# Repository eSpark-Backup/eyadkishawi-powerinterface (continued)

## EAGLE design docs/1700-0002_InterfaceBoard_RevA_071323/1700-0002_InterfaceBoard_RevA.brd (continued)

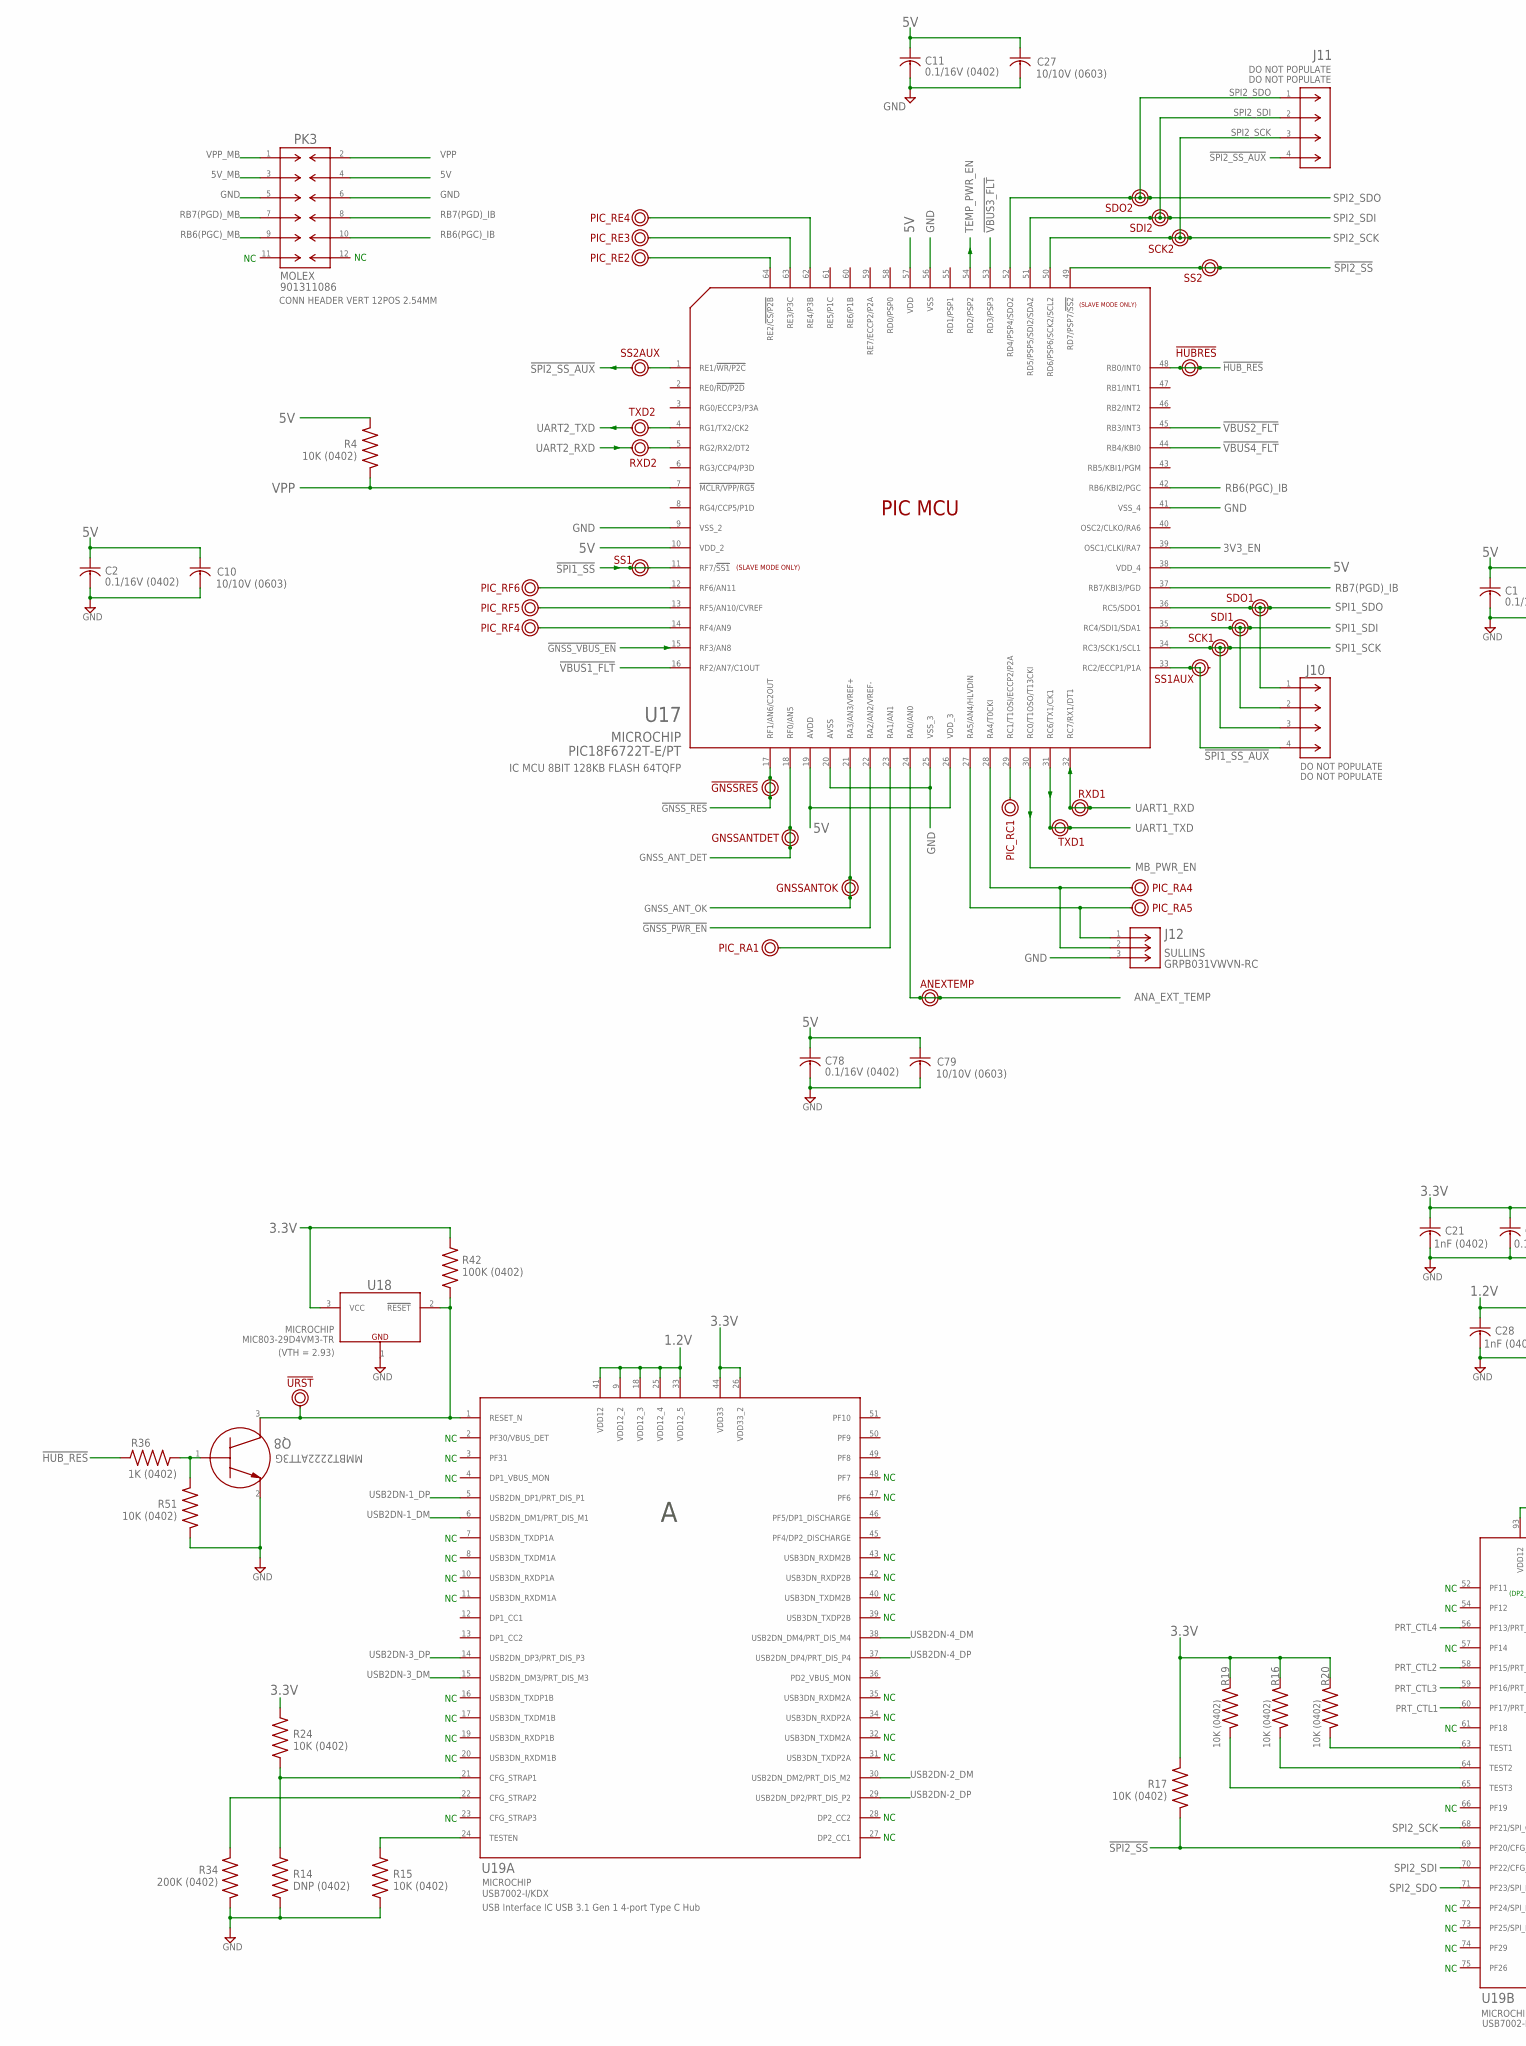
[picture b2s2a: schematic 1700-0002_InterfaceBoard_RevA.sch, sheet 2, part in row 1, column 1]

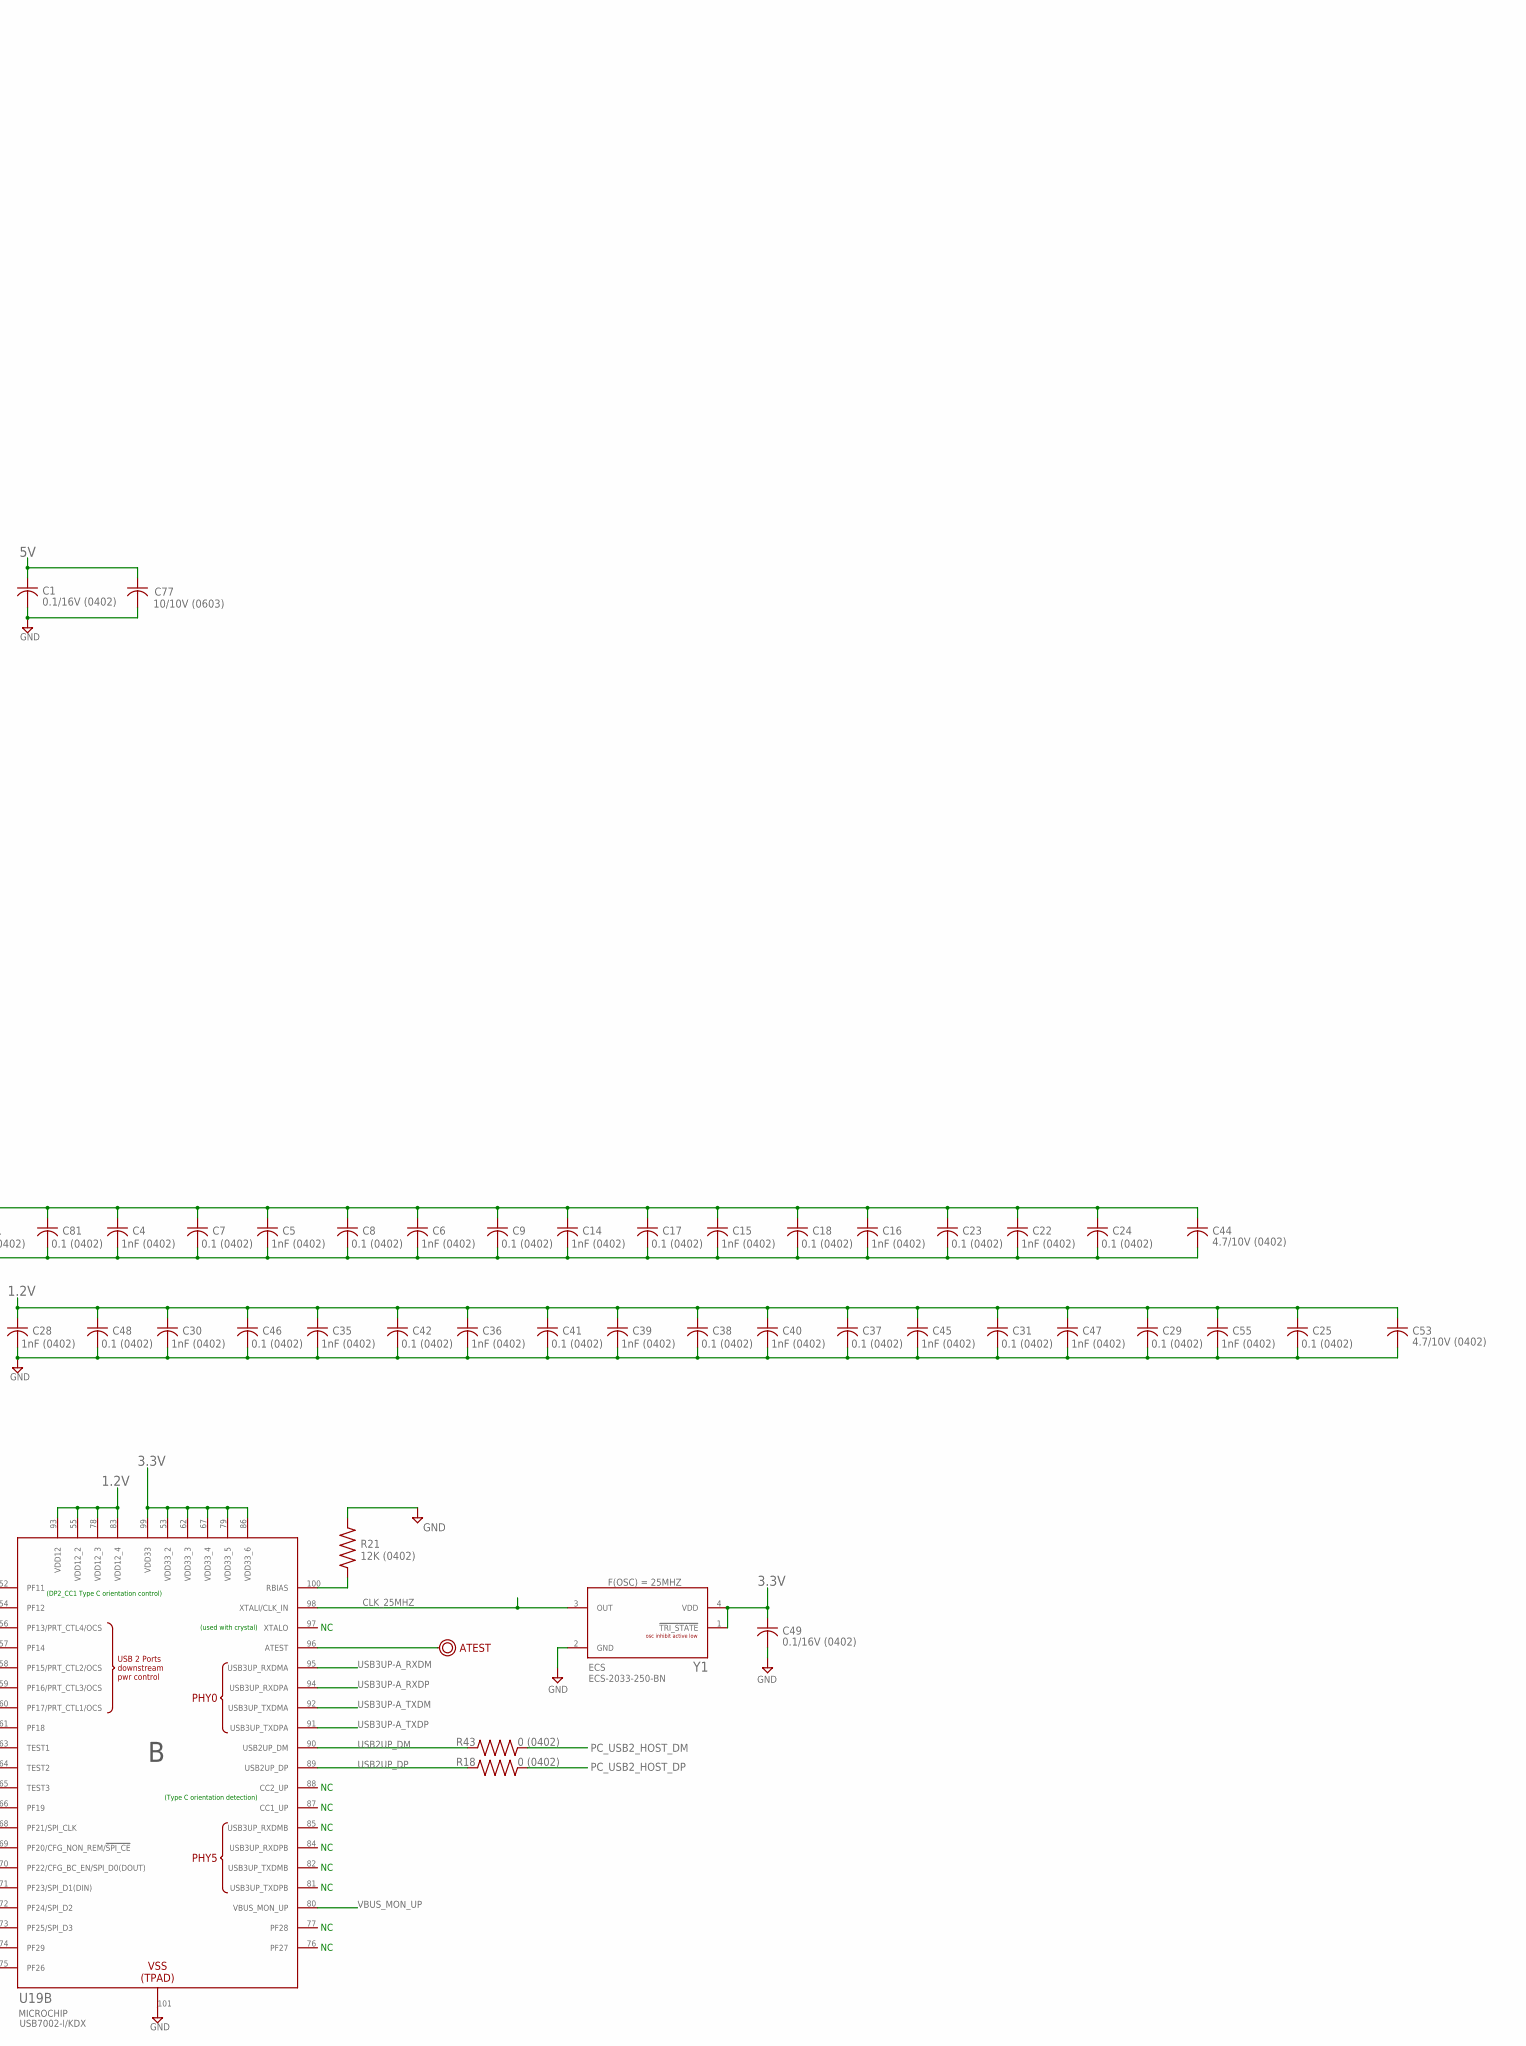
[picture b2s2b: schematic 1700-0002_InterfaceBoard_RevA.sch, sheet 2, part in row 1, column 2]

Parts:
!GNSSRES: TST_POINT_PTH_20X40MIL_2PIN
!HUBRES: TST_POINT_PTH_20X40MIL_2PIN
!URST: TST_POINT_PTH_042-OCT
ANEXTEMP: TST_POINT_PTH_20X40MIL_2PIN
ATEST: TST_POINT_PTH_042-OCT
C1, C2, C11, C49, C78: 0.1/16V (0402); G-155_MUR
C4, C5, C6, C14, C15, C16, C21, C22, C28, C30, C35, C36, C39, C40, C45, C47, C55: 1nF (0402); G-155_MUR; MANUFACTURER_PART_NUMBER C0402C102K4RAC7867
C7, C8, C9, C17, C18, C23, C24, C25, C29, C31, C37, C38, C41, C42, C46, C48, C81: 0.1 (0402); G-155_MUR
C10, C27, C77, C79: 10/10V (0603); CAP_C1608_TDK; MANUFACTURER_PART_NUMBER GRM188D71A106KA73D
C44, C53: 4.7/10V (0402); G-155_MUR; MANUFACTURER_PART_NUMBER C1005X5R1A475K050BE
GNSSANTDET: TST_POINT_PTH_20X40MIL_2PIN
GNSSANTOK: TST_POINT_PTH_20X40MIL_2PIN
J10, J11: MOLEX_VERT-HDR_1718561004; MOLEX_VERT-HDR_171861004; MANUFACTURER_PART_NUMBER DO NOT POPULATE
J12: SULLINS_MALE-HDR_050_GRPB031VWVN-RC; CONN_GRPB031VWVN-RC_SUL
PIC_RA1, PIC_RA4, PIC_RA5: TST_POINT_PTH_042-OCT
PIC_RC1: TST_POINT_PTH_042-OCT
PIC_RE2, PIC_RE3, PIC_RE4: TST_POINT_PTH_042-OCT
PIC_RF4, PIC_RF5, PIC_RF6: TST_POINT_PTH_042-OCT
PK3: CON_MOLEX_901311086; CON_901311086_MOL
Q8: MMBT2222ATT3G; SC-75(SOT-416)_ONSEMI
R4, R15, R16, R17, R19, R20, R24, R51: 10K (0402); RESC1005X35N
R14: DNP (0402); RESC1005X35N; MANUFACTURER_PART_NUMBER DO NOT POPULATE
R18, R43: 0 (0402); RESC1005X35N; MANUFACTURER_PART_NUMBER CRCW04020000Z0EDC
R21: 12K (0402); RESC1005X35N; MANUFACTURER_PART_NUMBER CRCW040212K0FKEDC
R34: 200K (0402); RESC1005X35N; MANUFACTURER_PART_NUMBER CRCW0402200KFKED
R36: 1K (0402); RESC1005X35N; MANUFACTURER_PART_NUMBER CRCW04021K00FKEDC
R42: 100K (0402); RESC1005X35N; MANUFACTURER_PART_NUMBER CRCW0402100KFKEDC
RXD1, RXD2: TST_POINT_PTH_20X40MIL_2PIN
SCK1, SCK2: TST_POINT_PTH_20X40MIL_2PIN
SDI1, SDI2: TST_POINT_PTH_20X40MIL_2PIN
SDO1, SDO2: TST_POINT_PTH_20X40MIL_2PIN
SS1, SS1AUX, SS2, SS2AUX: TST_POINT_PTH_20X40MIL_2PIN
TXD1, TXD2: TST_POINT_PTH_20X40MIL_2PIN
U17: PIC18F6627T-E/PT; TQFP64_10X10MC_MCH; MANUFACTURER_PART_NUMBER PIC18F6722T-E/PT
U18: (VTH = 2.93); SOT-23_M3_MCH
U19: MICROCHIP_USB7002-I/KDX; VQFN100_KDX_MCH; PART_DESC USB Interface IC USB 3.1 Gen 1 4-port T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
Y1: F(OSC) = 25MHZ; OSC_ECS-2033-250-BN

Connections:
1.2V: C25.1, C28.1, C29.1, C30.1, C31.1, C35.1, C36.1, C37.1, C38.1, C39.1, C40.1, C41.1, C42.1, C45.1, C46.1, C47.1, C48.1, C53.1, C55.1, U19.9 (VDD12_2), U19.18 (VDD12_3), U19.25 (VDD12_4), U19.33 (VDD12_5), U19.41 (VDD12), U19.55 (VDD12_2), U19.78 (VDD12_3), U19.83 (VDD12_4), U19.93 (VDD12); also elsewhere on the board
3.3V: C4.1, C5.1, C6.1, C7.1, C8.1, C9.1, C14.1, C15.1, C16.1, C17.1, C18.1, C21.1, C22.1, C23.1, C24.1, C44.1, C49.1, C81.1, R16.1, R17.1, R19.1, R20.1, R24.1, R42.1, U18.3 (VCC), U19.26 (VDD33_2), U19.44 (VDD33), U19.53 (VDD33_2), U19.62 (VDD33_3), U19.67 (VDD33_4), U19.79 (VDD33_5), U19.86 (VDD33_6), U19.99 (VDD33), Y1.1 (!TRI_STATE), Y1.4 (VDD); also elsewhere on the board
3V3_EN: U17.39 (OSC1/CLKI/RA7); also elsewhere on the board
5V: C1.1, C2.1, C10.1, C11.1, C27.1, C77.1, C78.1, C79.1, PK3.4, R4.1, U17.10 (VDD_2), U17.19 (AVDD), U17.26 (VDD_3), U17.38 (VDD_4), U17.57 (VDD); also elsewhere on the board
5V_MB: PK3.3; also elsewhere on the board
!GNSS_PWR_EN: U17.22 (RA2/AN2/VREF-); also elsewhere on the board
!GNSS_RES: !GNSSRES.P$1, !GNSSRES.P$2, U17.17 (RF1/AN6/C2OUT); also elsewhere on the board
!GNSS_VBUS_EN: U17.15 (RF3/AN8); also elsewhere on the board
!HUB_RES: !HUBRES.P$1, !HUBRES.P$2, R36.1, U17.48 (RB0/INT0)
!SPI1_SS: SS1.P$2, U17.11 (RF7/!SS1); also elsewhere on the board
!SPI1_SS_AUX: J10.4, SS1AUX.P$2, U17.33 (RC2/ECCP1/P1A)
!SPI2_SS: R17.2, SS2.P$1, SS2.P$2, U17.49 (RD7/PSP7/!SS2), U19.69 (PF20/CFG_NON_REM/!SPI_CE)
!SPI2_SS_AUX: J11.4, SS2AUX.P$2
!URST: !URST.P$1, Q8.3 (C), R42.2, U18.2 (!RESET), U19.1 (RESET_N)
!VBUS1_FLT: U17.16 (RF2/AN7/C1OUT); also elsewhere on the board
!VBUS2_FLT: U17.45 (RB3/INT3); also elsewhere on the board
!VBUS3_FLT: U17.53 (RD3/PSP3); also elsewhere on the board
!VBUS4_FLT: U17.44 (RB4/KBI0); also elsewhere on the board
ANA_EXT_TEMP: ANEXTEMP.P$1, ANEXTEMP.P$2, U17.24 (RA0/AN0); also elsewhere on the board
CLK_25MHZ: U19.98 (XTALI/CLK_IN), Y1.3 (OUT)
GND: C1.2, C2.2, C4.2, C5.2, C6.2, C7.2, C8.2, C9.2, C10.2, C11.2, C14.2, C15.2, C16.2, C17.2, C18.2, C21.2, C22.2, C23.2, C24.2, C25.2, C27.2, C28.2, C29.2, C30.2, C31.2, C35.2, C36.2, C37.2, C38.2, C39.2, C40.2, C41.2, C42.2, C44.2, C45.2, C46.2, C47.2, C48.2, C49.2, C53.2, C55.2, C77.2, C78.2, C79.2, C81.2, J12.3, PK3.5, PK3.6, Q8.2 (E), R14.2, R15.2, R21.1, R34.2, R51.2, U17.9 (VSS_2), U17.20 (AVSS), U17.25 (VSS_3), U17.41 (VSS_4), U17.56 (VSS), U18.1 (GND), U19.101 (VSS), Y1.2 (GND); also elsewhere on the board
GNSS_ANT_DET: GNSSANTDET.P$1, GNSSANTDET.P$2, U17.18 (RF0/AN5); also elsewhere on the board
GNSS_ANT_OK: GNSSANTOK.P$1, GNSSANTOK.P$2, U17.21 (RA3/AN3/VREF+); also elsewhere on the board
MB_PWR_EN: U17.30 (RC0/T1OSO/T13CKI); also elsewhere on the board
unnamed: PIC_RF6.P$1, U17.12 (RF6/AN11)
unnamed: TXD2.P$1, U17.4 (RG1/TX2/CK2)
unnamed: R14.1, R24.2, U19.21 (CFG_STRAP1)
unnamed: R34.1, U19.22 (CFG_STRAP2)
unnamed: R15.1, U19.24 (TESTEN)
unnamed: R20.2, U19.63 (TEST1)
unnamed: R19.2, U19.65 (TEST3)
unnamed: R21.2, U19.100 (RBIAS)
unnamed: R16.2, U19.64 (TEST2)
unnamed: ATEST.P$1, U19.96 (ATEST)
unnamed: PIC_RF5.P$1, U17.13 (RF5/AN10/CVREF)
unnamed: PIC_RF4.P$1, U17.14 (RF4/AN9)
unnamed: PIC_RA1.P$1, U17.23 (RA1/AN1)
unnamed: RXD2.P$1, U17.5 (RG2/RX2/DT2)
unnamed: SS2AUX.P$1, U17.1 (RE1/!WR/P2C)
unnamed: J12.1, PIC_RA5.P$1, U17.27 (RA5/AN4/HLVDIN)
unnamed: J12.2, PIC_RA4.P$1, U17.28 (RA4/T0CKI)
unnamed: PIC_RC1.P$1, U17.29 (RC1/T1OSI/ECCP2/P2A)
unnamed: PIC_RE2.P$1, U17.64 (RE2/!CS/P2B)
unnamed: PIC_RE3.P$1, U17.63 (RE3/P3C)
unnamed: PIC_RE4.P$1, U17.62 (RE4/P3B)
PC_USB2_HOST_DM: R43.2; also elsewhere on the board
PC_USB2_HOST_DP: R18.2; also elsewhere on the board
PRT_CTL1: U19.60 (PF17/PRT_CTL1/OCS); also elsewhere on the board
PRT_CTL2: U19.58 (PF15/PRT_CTL2/OCS); also elsewhere on the board
PRT_CTL3: U19.59 (PF16/PRT_CTL3/OCS); also elsewhere on the board
PRT_CTL4: U19.56 (PF13/PRT_CTL4/OCS); also elsewhere on the board
PWR_BYP3: Q8.1 (B), R36.2, R51.1
RB6(PGC)_IB: PK3.10, U17.42 (RB6/KBI2/PGC)
RB6(PGC)_MB: PK3.9; also elsewhere on the board
RB7(PGD)_IB: PK3.8, U17.37 (RB7/KBI3/PGD)
RB7(PGD)_MB: PK3.7; also elsewhere on the board
SPI1_SCK: J10.3, SCK1.P$1, SCK1.P$2, U17.34 (RC3/SCK1/SCL1); also elsewhere on the board
SPI1_SDI: J10.2, SDI1.P$1, SDI1.P$2, U17.35 (RC4/SDI1/SDA1); also elsewhere on the board
SPI1_SDO: J10.1, SDO1.P$1, SDO1.P$2, U17.36 (RC5/SDO1); also elsewhere on the board
SPI2_SCK: J11.3, SCK2.P$1, SCK2.P$2, U17.50 (RD6/PSP6/SCK2/SCL2), U19.68 (PF21/SPI_CLK)
SPI2_SDI: J11.2, SDI2.P$1, SDI2.P$2, U17.51 (RD5/PSP5/SDI2/SDA2), U19.70 (PF22/CFG_BC_EN/SPI_D0(DOUT))
SPI2_SDO: J11.1, SDO2.P$1, SDO2.P$2, U17.52 (RD4/PSP4/SDO2), U19.71 (PF23/SPI_D1(DIN))
TEMP_PWR_EN: U17.54 (RD2/PSP2); also elsewhere on the board
UART1_RXD: RXD1.P$1, RXD1.P$2, U17.32 (RC7/RX1/DT1); also elsewhere on the board
UART1_TXD: TXD1.P$1, TXD1.P$2, U17.31 (RC6/TX1/CK1); also elsewhere on the board
UART2_RXD: RXD2.P$2; also elsewhere on the board
UART2_TXD: TXD2.P$2; also elsewhere on the board
USB2DN-1_DM: U19.6 (USB2DN_DM1/PRT_DIS_M1); also elsewhere on the board
USB2DN-1_DP: U19.5 (USB2DN_DP1/PRT_DIS_P1); also elsewhere on the board
USB2DN-2_DM: U19.30 (USB2DN_DM2/PRT_DIS_M2); also elsewhere on the board
USB2DN-2_DP: U19.29 (USB2DN_DP2/PRT_DIS_P2); also elsewhere on the board
USB2DN-3_DM: U19.15 (USB2DN_DM3/PRT_DIS_M3); also elsewhere on the board
USB2DN-3_DP: U19.14 (USB2DN_DP3/PRT_DIS_P3); also elsewhere on the board
USB2DN-4_DM: U19.38 (USB2DN_DM4/PRT_DIS_M4); also elsewhere on the board
USB2DN-4_DP: U19.37 (USB2DN_DP4/PRT_DIS_P4); also elsewhere on the board
USB2UP_DM: R43.1, U19.90 (USB2UP_DM)
USB2UP_DP: R18.1, U19.89 (USB2UP_DP)
USB3UP-A_RXDM: U19.95 (USB3UP_RXDMA); also elsewhere on the board
USB3UP-A_RXDP: U19.94 (USB3UP_RXDPA); also elsewhere on the board
USB3UP-A_TXDM: U19.92 (USB3UP_TXDMA); also elsewhere on the board
USB3UP-A_TXDP: U19.91 (USB3UP_TXDPA); also elsewhere on the board
VBUS_MON_UP: U19.80 (VBUS_MON_UP); also elsewhere on the board
VPP: PK3.2, R4.2, U17.7 (!MCLR/VPP/RG5)
VPP_MB: PK3.1; also elsewhere on the board

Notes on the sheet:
(DP2_CC1 Type C orientation control)
(Type C orientation detection)
(used with crystal)

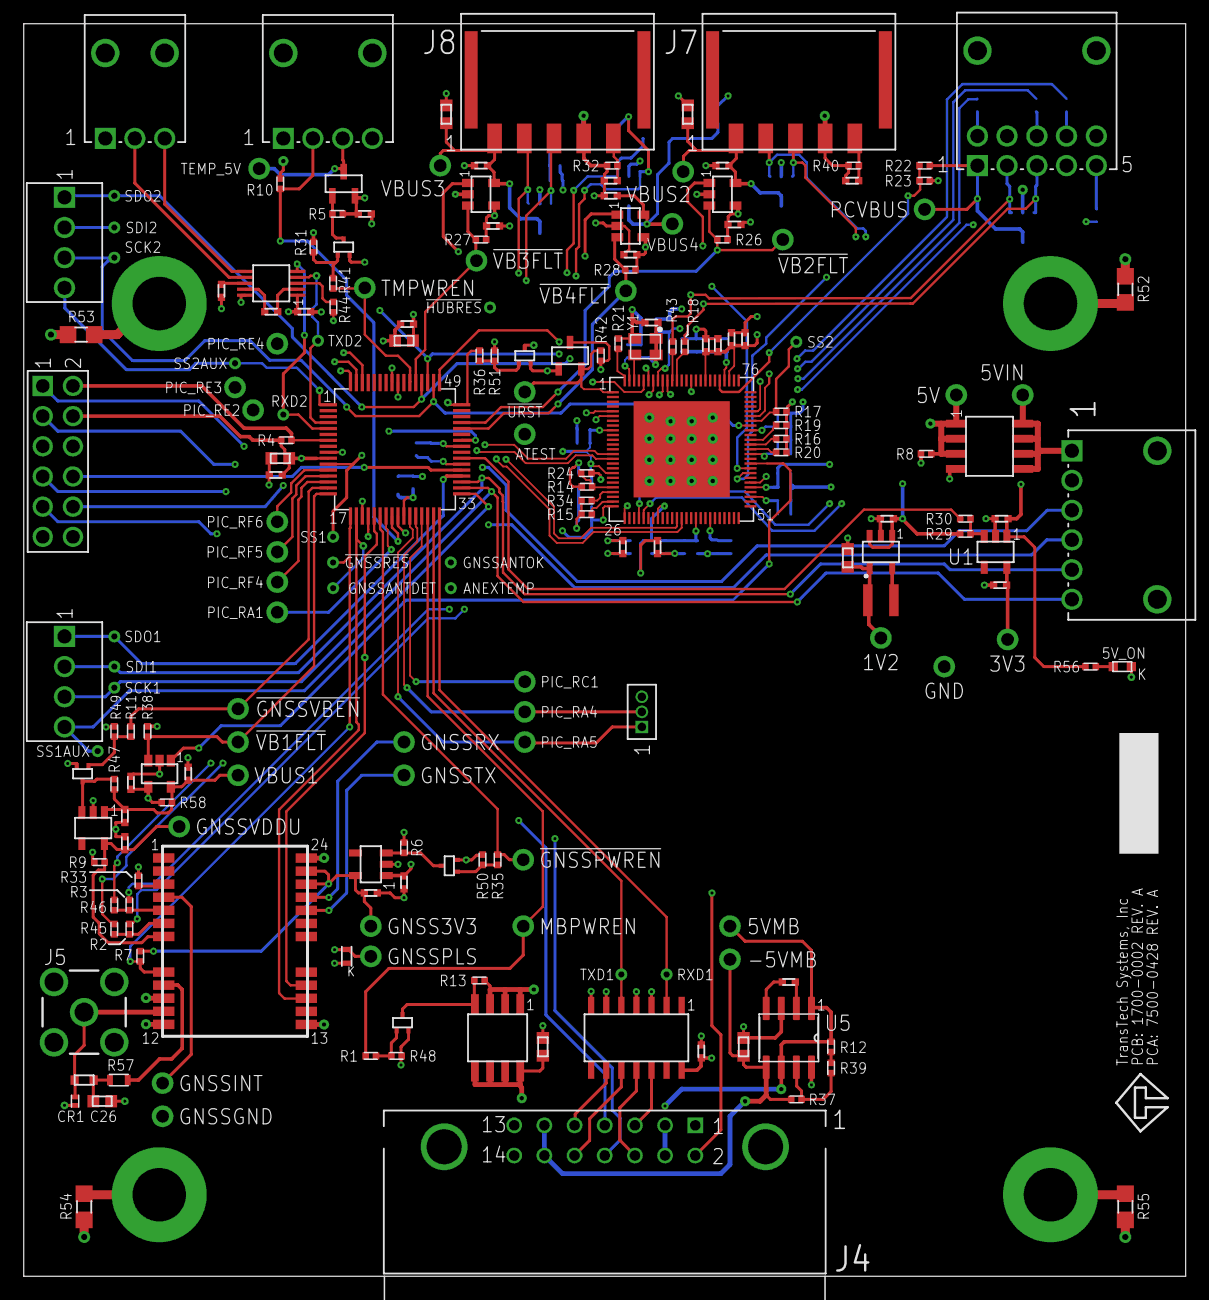
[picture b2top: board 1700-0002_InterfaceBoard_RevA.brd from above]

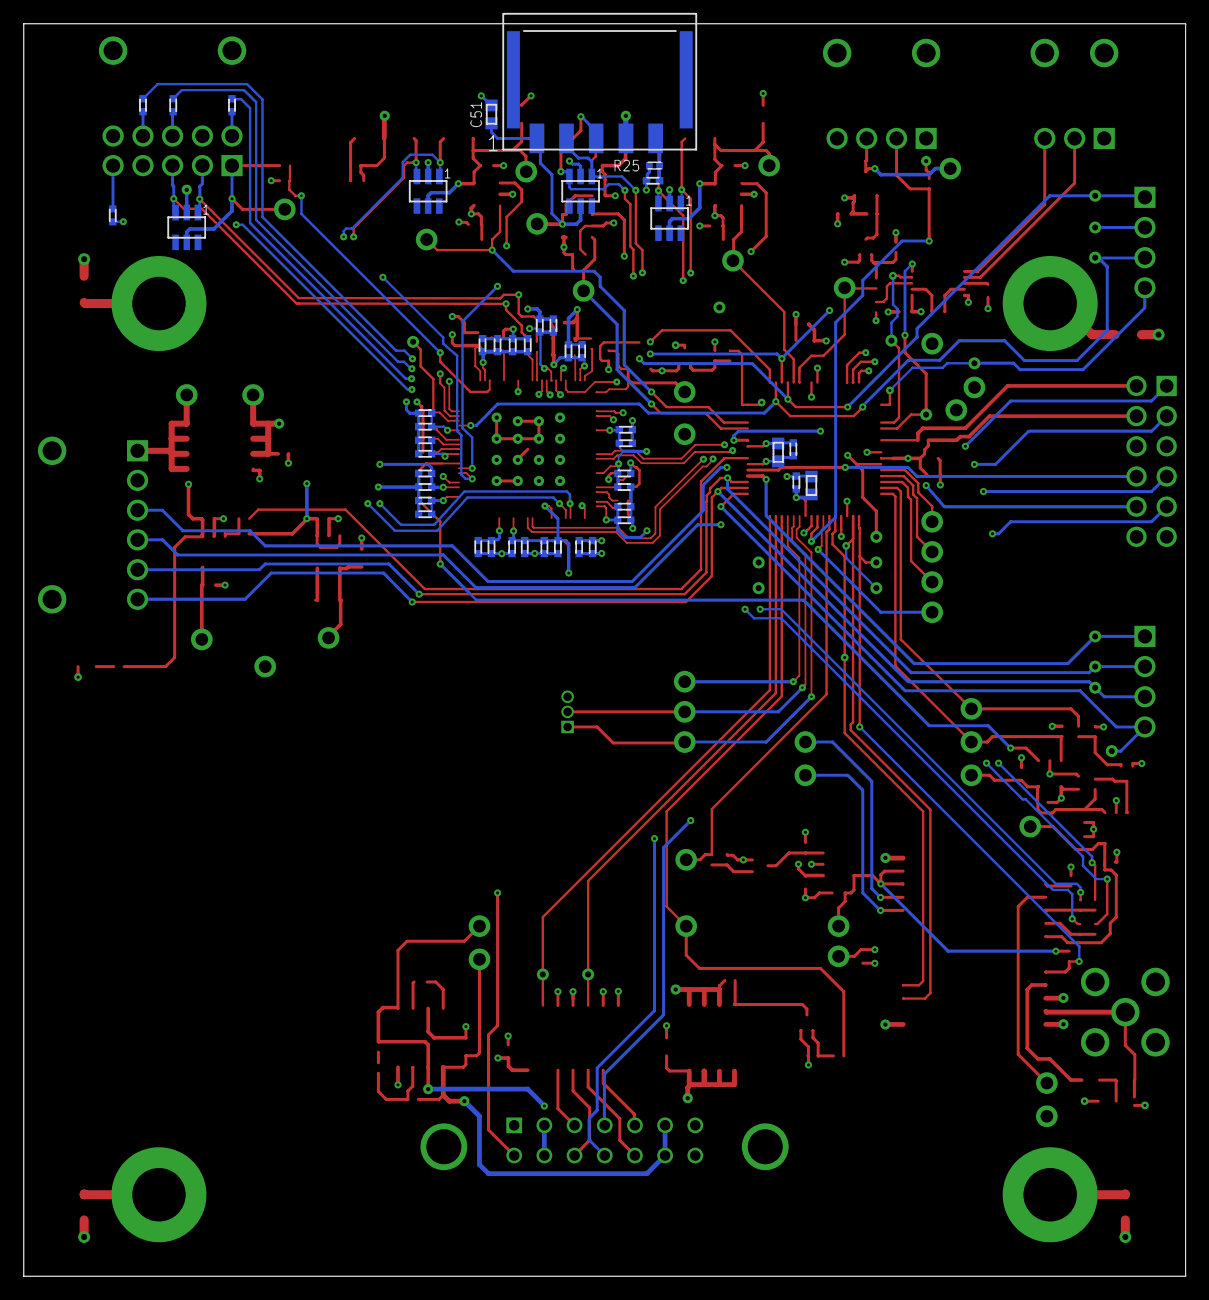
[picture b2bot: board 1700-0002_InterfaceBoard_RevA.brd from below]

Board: 4 copper layers, 97.8 x 105.4 mm, 247 parts (46 on the bottom side), 140 nets.

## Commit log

2024-07-11 pushed client files
2024-07-11 #1 Updated files
2024-07-11 #2 Design In progress
2024-07-12 added gitignore and removed extra files
2024-07-13 #2 Schematic Completed
2024-07-13 #2 do not populate statement added
2024-07-14 #2 PCB file added: Component imported: Rest remaining.
2024-07-15 #2 Mounting hole and respective resistor added to Schematic and imported to PCB
2024-07-15 #1 Design in Progress
2024-07-15 #1 Eagle files Deliverables Generate.
2024-07-15 #2 eagle Files deliverables Generate.
2024-07-15 #2 renderings added.
2024-07-18 #2 Eagle Gerber added
2024-07-18 #1 Eagle gerbers added.
2024-07-18 #2 Eagle gerber Updated.
2024-07-19 #1 Schematic completed
2024-07-22 Placement in progress
2024-07-23 #2 resistor updated due to footprint and Placement in Progress
2024-07-24 #1 Placement done Routing in progress
2024-07-25 #1 Routing in Progress
2024-07-29 #1 Routing completed
2024-07-30 #1 Logo added
2024-07-31 #2 Routing in progress
2024-08-01 #2 completed
2024-08-01 #4 In-progress.
2024-08-02 #4 Client BOM update.
2024-08-02 #2 Client BOM added
2024-08-02 #4 Deliverables Generated after minor corrections in Routing.
2024-08-02 #5 In-progress.
2024-08-04 #3 Corrections in Schematic of Power Baord.
2024-08-04 #4 Fresh Deliverables along with Client BOM Generated for Power Board.
2024-08-05 #3 Correction done, BOM and Deliverables generated
2024-08-05 #3 Overlay corrected for GNSS TX, RX rest all set Deliverables generated accordinly
2024-08-05 #5 Fresh Deliverables generated: BOM updated.
2024-08-05 Removed gereber.zip (extra)
2024-08-05 Folder readjustment (minor)
2024-08-12 #3 Some components marked as DNP mention in issue
2024-08-12 #3 netlabel updated mention in issue
2024-08-13 Interface board completed with changes mention in #3 along with Deliverables and BOM
2024-08-13 Schematic PCB updated acc to changes mention in #3 #4 Deliverables and BOM updated too
